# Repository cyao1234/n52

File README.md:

# n52 stamp

nRF52 stamp devboard with castellated holes on all 3 edges and a low profile,
allowing it to be easily soldered onto a carrier board, without having to deal with
the aQFN nRF52840 footprint. The board breaks out 36 I/O pins, and also has an
embedded 24 pin e-ink connector.

The board can operate standalone for direct wireless communication with host devices, or function as a carrier board for more complex projects. Key features include low current consumption, easy usability, and a streamlined design that prioritizes rapid prototyping and deployment.

The board's 36 broken-out I/O pins provide extensive flexibility for sensor integration, peripheral control, and data communication.

Features:
- Integrated power path
- LiPo charger
- Eink driver
- Low current consumption
- Easy to use
- Castellated edges

The board uses a nrf52 design to allow for bluetooth communication, and has all that is needed to directly communicate via bluetooth to a host. No external parts needed, but it can also act as an carrier board

Pins:
* LED0 = P0.18
* LED1 = P0.17
* E-Ink
  * BUSY   = P0.26
  * nRESET = P0.04
  * nD/C   = P0.06
  * nCS    = P0.08
  * CLK    = P1.09
  * MOSI   = P0.11

The best way to program the board and use it is to use [Zephyr](https://docs.zephyrproject.org/)

All sources are present in the repo

| Item | Cost | Where |
| ---- | ---- | ----- |
| PCB + PCBA | $160 | JLC |

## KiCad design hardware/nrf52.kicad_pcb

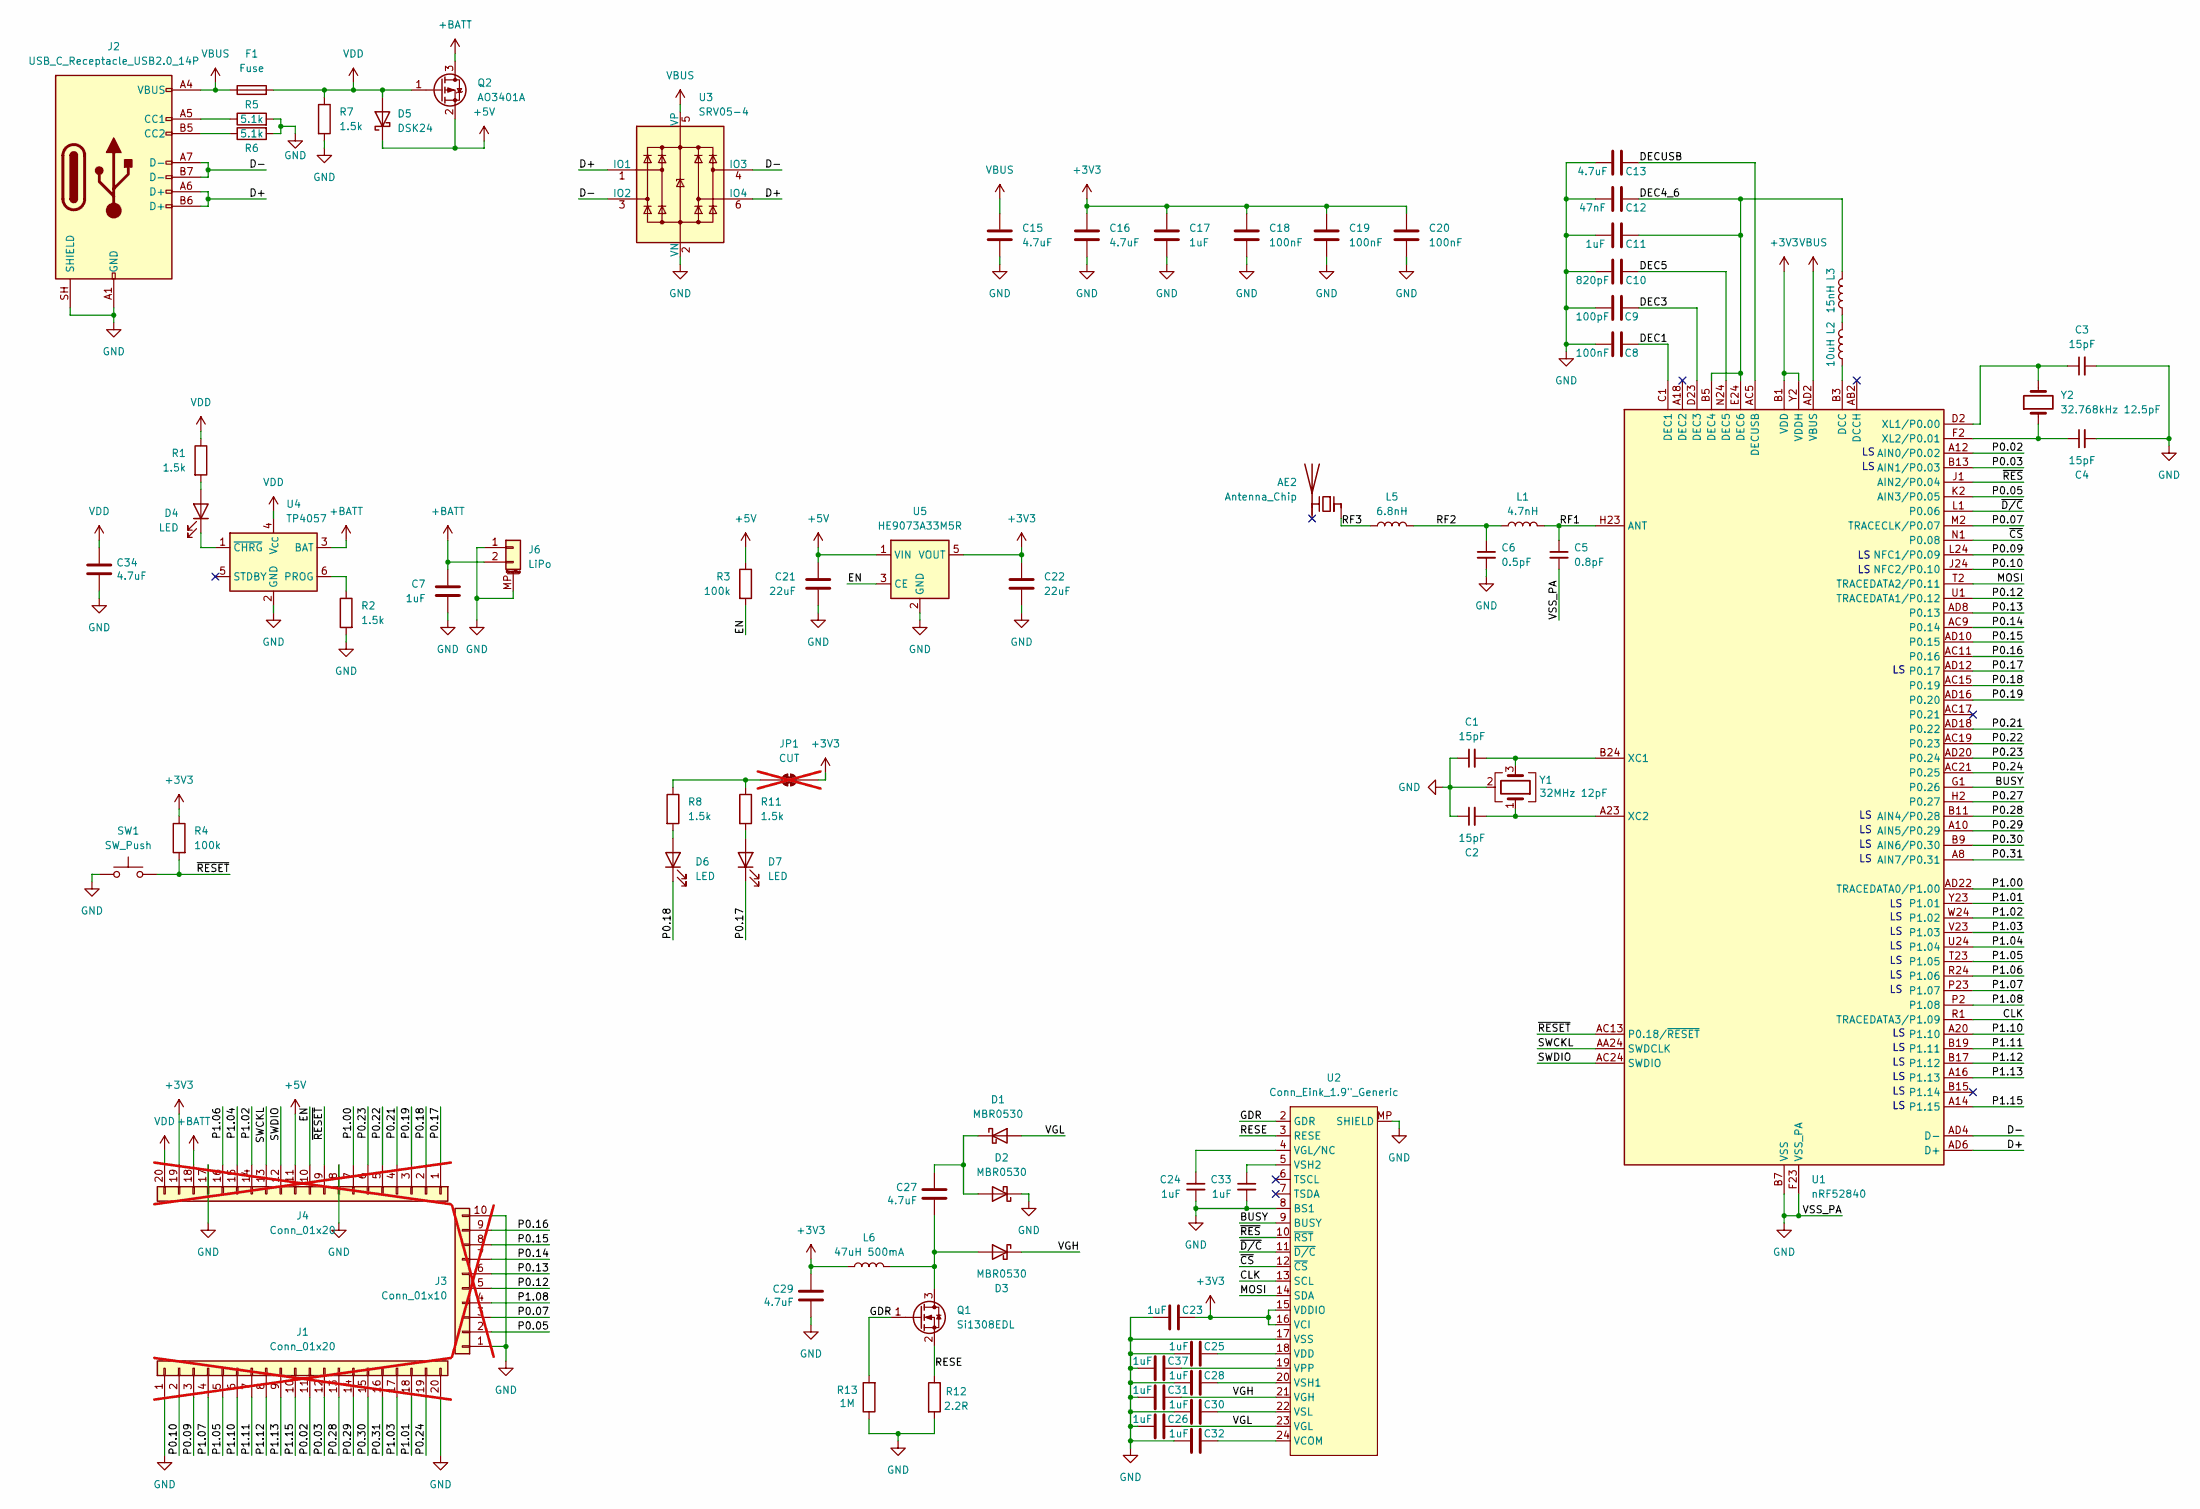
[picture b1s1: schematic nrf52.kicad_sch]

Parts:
AE2: Antenna_Chip; Walsin_RFANT3216120A5T; LCSC Part # C127629
C1, C2, C3, C4: 15pF; C_0402_1005Metric; LCSC Part # C1548
C5: 0.8pF; C_0402_1005Metric; LCSC Part # C76915
C6: 0.5pF; C_0402_1005Metric; LCSC Part # C76912
C7, C11, C17, C23, C24, C25, C26, C28, C30, C31, C32, C33, C37: 1uF; C_0402_1005Metric; LCSC Part # C7472946
C8, C18, C19, C20: 100nF; C_0402_1005Metric; LCSC Part # C1525
C9: 100pF; C_0402_1005Metric; LCSC Part # C1546
C10: 820pF; C_0402_1005Metric; LCSC Part # C107031
C12: 47nF; C_0402_1005Metric; LCSC Part # C272875
C13, C15, C16: 4.7uF; C_0603_1608Metric; LCSC Part # C380325
C21, C22: 22uF; C_0603_1608Metric; LCSC Part # C380323
C27, C29, C34: 4.7uF; C_0402_1005Metric; LCSC Part # C380302
D1, D2, D3: MBR0530; D_SOD-123; LCSC Part # C7436545
D4, D6, D7: LED; LED_0402_1005Metric; LCSC Part # C51933306
D5: DSK24; D_SOD-123F; LCSC Part # C22466352
F1: Fuse; Fuse_0805_2012Metric; LCSC Part # C46640991
J1, J4: Conn_01x20; Castellated_1x20_P2.54mm_Vertical; not fitted
J2: USB_C_Receptacle_USB2.0_14P; USB_C_Receptacle_SHOU-HAN_TYPE-16P; LCSC Part # C2906290
J3: Conn_01x10; Castellated_1x10_P2.54mm_Vertical; not fitted
J6: LiPo; HCTL_JST_PH_HC-PH-2AWT-B_2P; LCSC Part # C19633668
JP1: CUT; SolderJumper-2_Bridged_Pad_Small; not fitted
L1: 4.7nH; L_0402_1005Metric; LCSC Part # C86065
L2: 10uH; L_0603_1608Metric; LCSC Part # C281107
L3: 15nH; L_0402_1005Metric; LCSC Part # C86059
L5: 6.8nH; L_0402_1005Metric; LCSC Part # C96056
L6: 47uH 500mA; L_APV_ANR3015; LCSC Part # C7427088
Q1: Si1308EDL; SOT-323_SC-70; LCSC Part # C7603347
Q2: AO3401A; SOT-23; LCSC Part # C347476
R1, R2, R7, R8, R11: 1.5k; R_0402_1005Metric; LCSC Part # C114451
R3, R4: 100k; R_0402_1005Metric; LCSC Part # C481918
R5, R6: 5.1k; R_0402_1005Metric; LCSC Part # C2906874
R12: 2.2R; R_0402_1005Metric; LCSC Part # C2906922
R13: 1M; R_0402_1005Metric; LCSC Part # C93949
SW1: SW_Push; SW_Push_SPST_TSA016; LCSC Part # C2888428
U1: nRF52840; Nordic_AQFN-73-1EP_7x7mm_P0.5mm_Small; LCSC Part # C190794
U2: Conn_Eink_1.9"_Generic; HCTL_HC-FPC-05-09-24RLTAG-1MP_P0.5mm_Horizontal; LCSC Part # C5213757
U3: SRV05-4; SOT-23-6; LCSC Part # C2836319
U4: TP4057; TSOT-23-6; LCSC Part # C5380673
U5: HE9073A33M5R; SOT-23-5; LCSC Part # C723789
Y1: 32MHz 12pF; Crystal_SMD_2016-4Pin_2.0x1.6mm; LCSC Part # C383840
Y2: 32.768kHz 12.5pF; Crystal_SMD_2012-2Pin_2.0x1.2mm; LCSC Part # C55208

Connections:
+3V3: C16.1, C17.1, C18.1, C19.1, C20.1, C22.1, C23.1, C29.1, J4.19, JP1.2 (B), L6.1, R4.1, U1.A22 (VDD), U1.AD14 (VDD), U1.AD23 (VDD), U1.B1 (VDD), U1.W1 (VDD), U1.Y2 (VDDH), U2.15 (VDDIO), U2.16 (VCI), U5.5 (VOUT)
+5V: C21.1, D5.1 (K), J4.11, Q2.2 (S), R3.1, U5.1 (VIN)
+BATT: C7.1, J4.18, J6.2, Q2.3 (D), U4.3 (BAT)
/BUSY: U1.G1 (P0.26), U2.9 (BUSY)
/CLK: U1.R1 (TRACEDATA3/P1.09), U2.13 (SCL)
/D+: J2.A6 (D+), J2.B6 (D+), U1.AD6 (D+), U3.1 (IO1), U3.6 (IO4)
/D-: J2.A7 (D-), J2.B7 (D-), U1.AD4 (D-), U3.3 (IO2), U3.4 (IO3)
/DEC1: C8.2, U1.C1 (DEC1)
/DEC3: C9.2, U1.D23 (DEC3)
/DEC4_6: C11.2, C12.2, L3.2, U1.B5 (DEC4), U1.E24 (DEC6)
/DEC5: C10.2, U1.N24 (DEC5)
/DECUSB: C13.2, U1.AC5 (DECUSB)
/EN: J4.10, R3.2, U5.3 (CE)
/GDR: Q1.1 (G), R13.2, U2.2 (GDR)
/MOSI: U1.T2 (TRACEDATA2/P0.11), U2.14 (SDA)
/P0.02: J1.11, U1.A12 (AIN0/P0.02)
/P0.03: J1.12, U1.B13 (AIN1/P0.03)
/P0.05: J3.2, U1.K2 (AIN3/P0.05)
/P0.07: J3.3, U1.M2 (TRACECLK/P0.07)
/P0.09: J1.3, U1.L24 (NFC1/P0.09)
/P0.10: J1.2, U1.J24 (NFC2/P0.10)
/P0.12: J3.5, U1.U1 (TRACEDATA1/P0.12)
/P0.13: J3.6, U1.AD8 (P0.13)
/P0.14: J3.7, U1.AC9 (P0.14)
/P0.15: J3.8, U1.AD10 (P0.15)
/P0.16: J3.9, U1.AC11 (P0.16)
/P0.17: D7.1 (K), J4.1, U1.AD12 (P0.17)
/P0.18: D6.1 (K), J4.2, U1.AC15 (P0.19)
/P0.19: J4.3, U1.AD16 (P0.20)
/P0.21: J4.4, U1.AD18 (P0.22)
/P0.22: J4.5, U1.AC19 (P0.23)
/P0.23: J4.6, U1.AD20 (P0.24)
/P0.24: J1.19, U1.AC21 (P0.25)
/P0.27: U1.H2 (P0.27)
/P0.28: J1.13, U1.B11 (AIN4/P0.28)
/P0.29: J1.14, U1.A10 (AIN5/P0.29)
/P0.30: J1.15, U1.B9 (AIN6/P0.30)
/P0.31: J1.16, U1.A8 (AIN7/P0.31)
/P1.00: J4.7, U1.AD22 (TRACEDATA0/P1.00)
/P1.01: J1.18, U1.Y23 (P1.01)
/P1.02: J4.14, U1.W24 (P1.02)
/P1.03: J1.17, U1.V23 (P1.03)
/P1.04: J4.15, U1.U24 (P1.04)
/P1.05: J1.5, U1.T23 (P1.05)
/P1.06: J4.16, U1.R24 (P1.06)
/P1.07: J1.4, U1.P23 (P1.07)
/P1.08: J3.4, U1.P2 (P1.08)
/P1.10: J1.6, U1.A20 (P1.10)
/P1.11: J1.7, U1.B19 (P1.11)
/P1.12: J1.8, U1.B17 (P1.12)
/P1.13: J1.9, U1.A16 (P1.13)
/P1.15: J1.10, U1.A14 (P1.15)
/RESE: Q1.2 (S), R12.1, U2.3 (RESE)
/RF1: C5.1, L1.2, U1.H23 (ANT)
/RF2: C6.1, L1.1, L5.2
/RF3: AE2.1 (FEED_1), L5.1
/SWCKL: J4.13, U1.AA24 (SWDCLK)
/SWDIO: J4.12, U1.AC24 (SWDIO)
/VGH: C31.1, D3.1 (K), U2.21 (VGH)
/VGL: C26.1, D1.2 (A), U2.23 (VGL)
/~CS: U1.N1 (P0.08), U2.12 (~CS)
/~D/C: U1.L1 (P0.06), U2.11 (~D/C)
/~RESET: J4.9, R4.2, SW1.2, U1.AC13 (P0.18/~RESET)
/~RES: U1.J1 (AIN2/P0.04), U2.10 (~RST)
GND: C1.1, C2.1, C3.2, C4.2, C5.2, C6.2, C7.2, C8.1, C9.1, C10.1, C11.1, C12.1, C13.1, C15.2, C16.2, C17.2, C18.2, C19.2, C20.2, C21.2, C22.2, C23.2, C24.2, C25.2, C26.2, C28.2, C29.2, C30.2, C31.2, C32.2, C33.2, C34.2, C37.2, D2.1 (K), J1.1, J1.20, J2.A1 (GND), J2.A12 (GND), J2.B1 (GND), J2.B12 (GND), J2.SH (SHIELD), J3.1, J3.10, J4.8, J4.17, J6.1, J6.MP (MountPin), R2.2, R5.2, R6.2, R7.2, R12.2, R13.1, SW1.1, U1.B7 (VSS), U1.EP (VSS), U1.F23 (VSS_PA), U2.8 (BS1), U2.17 (VSS), U2.MP (SHIELD), U3.2 (VN), U4.2 (GND), U5.2 (GND), Y1.2 (G), Y1.4 (G)
unnamed: C27.1, D1.1 (K), D2.2 (A)
unnamed: C27.2, D3.2 (A), L6.2, Q1.3 (D)
unnamed: D4.2 (A), R1.2
unnamed: D4.1 (K), U4.1 (~CHRG)
unnamed: D6.2 (A), R8.2
unnamed: D7.2 (A), R11.2
unnamed: J2.A5 (CC1), R5.1
unnamed: J2.B5 (CC2), R6.1
unnamed: JP1.1 (A), R8.1, R11.1
unnamed: L2.2, L3.1
unnamed: L2.1, U1.B3 (DCC)
unnamed: C1.2, U1.B24 (XC1), Y1.3
unnamed: C2.2, U1.A23 (XC2), Y1.1
unnamed: C3.1, U1.D2 (XL1/P0.00), Y2.2
unnamed: C4.1, U1.F2 (XL2/P0.01), Y2.1
unnamed: C32.1, U2.24 (VCOM)
unnamed: C25.1, U2.18 (VDD)
unnamed: C24.1, U2.4 (VGL/NC)
unnamed: C37.1, U2.19 (VPP)
unnamed: C28.1, U2.20 (VSH1)
unnamed: C33.1, U2.5 (VSH2)
unnamed: C30.1, U2.22 (VSL)
unnamed: R2.1, U4.6 (PROG)
VBUS: C15.1, F1.1, J2.A4 (VBUS), J2.A9 (VBUS), J2.B4 (VBUS), J2.B9 (VBUS), U1.AD2 (VBUS), U3.5 (VP)
VDD: C34.1, D5.2 (A), F1.2, J4.20, Q2.1 (G), R1.1, R7.1, U4.4 (V_{CC})

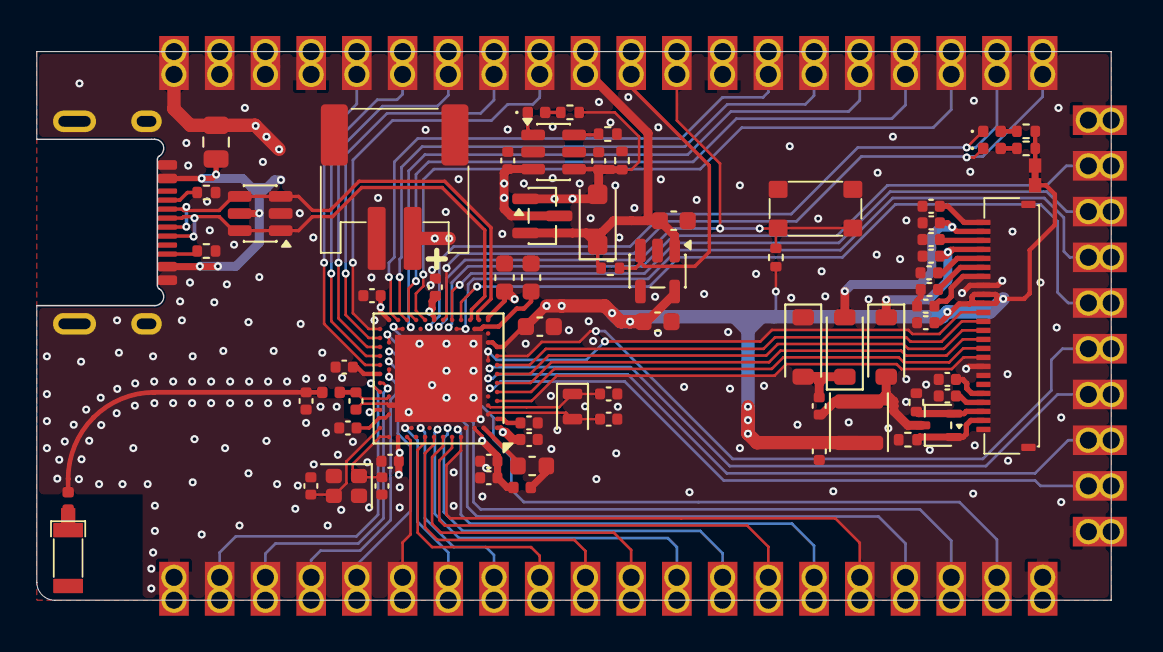
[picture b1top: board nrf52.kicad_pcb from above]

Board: 4 copper layers, 59.7 x 30.5 mm, 75 parts (0 on the bottom side), 89 nets.

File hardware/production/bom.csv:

Designator,Footprint,Quantity,Value,LCSC Part #
AE2,Walsin_RFANT3216120A5T,1,Antenna_Chip,C127629
"C1, C2, C3, C4",0402,4,15pF,C1548 
C10,0402,1,820pF,C107031
"C11, C17, C23, C24, C25, C26, C28, C30, C31, C32, C33, C37, C7",0402,13,1uF,C7472946
C12,0402,1,47nF,C272875
"C13, C15, C16",0603,3,4.7uF,C380325
"C18, C19, C20, C8",0402,4,100nF,C1525 
"C21, C22",0603,2,22uF,C380323
"C27, C29, C34",0402,3,4.7uF,C380302
C5,0402,1,0.8pF,C76915
C6,0402,1,0.5pF,C76912
C9,0402,1,100pF,C1546
"D1, D2, D3",D_SOD-123,3,MBR0530,C7436545
"D4, D6, D7",0402,3,LED,C51933306
D5,D_SOD-123F,1,DSK24,C22466352
F1,0805,1,Fuse,C46640991
J2,USB_C_Receptacle_SHOU-HAN_TYPE-16P,1,USB_C_Receptacle_USB2.0_14P,C2906290
J6,HCTL_JST_PH_HC-PH-2AWT-B_2P,1,LiPo,C19633668
L1,0402,1,4.7nH,C86065
L2,0603,1,10uH,C281107
L3,0402,1,15nH,C86059
L5,0402,1,6.8nH,C96056
L6,L_APV_ANR3015,1,47uH 500mA,C7427088
Q1,SOT-323_SC-70,1,Si1308EDL,C7603347
Q2,SOT-23,1,AO3401A,C347476
"R1, R11, R2, R7, R8",0402,5,1.5k,C114451
R12,0402,1,2.2R,C2906922
R13,0402,1,1M,C93949
"R3, R4",0402,2,100k,C481918
"R5, R6",0402,2,5.1k,C2906874
SW1,SW_Push_SPST_TSA016,1,SW_Push,C2888428
U1,Nordic_AQFN-73-1EP_7x7mm_P0.5mm_Small,1,nRF52840,C190794
U2,HCTL_HC-FPC-05-09-24RLTAG-1MP_P0.5mm_Horizontal,1,"Conn_Eink_1.9""_Generic",C5213757
U3,SOT-23-6,1,SRV05-4,C2836319
U4,TSOT-23-6,1,TP4057,C5380673
U5,SOT-23-5,1,HE9073A33M5R,C723789
Y1,Crystal_SMD_2016-4Pin_2.0x1.6mm,1,32MHz 12pF,C383840
Y2,Crystal_SMD_2012-2Pin_2.0x1.2mm,1,32.768kHz 12.5pF,C55208

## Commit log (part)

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2026-06-24 Init
2026-06-24 Update cost
